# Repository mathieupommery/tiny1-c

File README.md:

Breakout board for the tiny1-c thermal sensor in order to get acces to Vospi pins.

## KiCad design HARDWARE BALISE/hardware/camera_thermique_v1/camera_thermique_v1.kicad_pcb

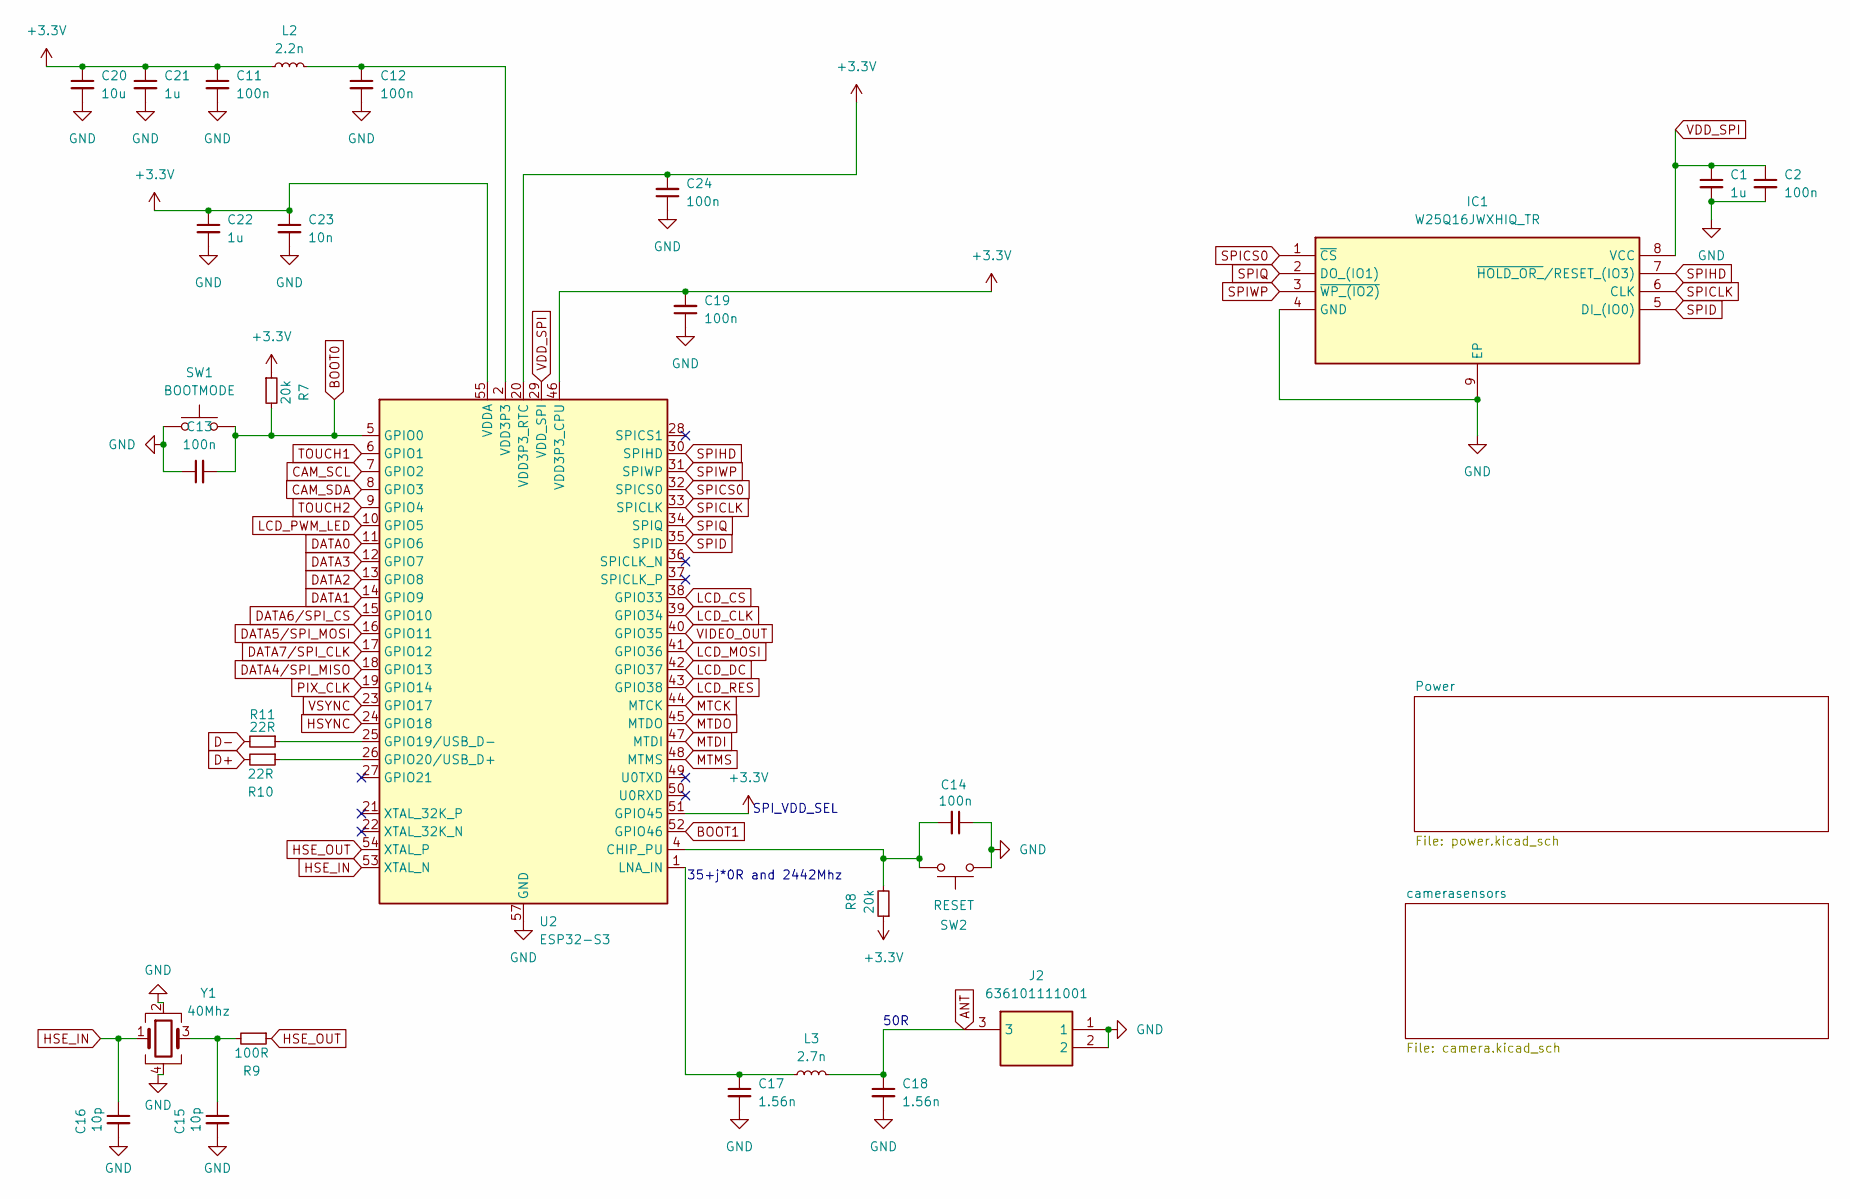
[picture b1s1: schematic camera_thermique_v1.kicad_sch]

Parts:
C1, C21, C22: 1u; C_0402_1005Metric_Pad0.74x0.62mm_HandSolder
C2, C11, C12, C13, C14, C19, C24: 100n; C_0201_0603Metric_Pad0.64x0.40mm_HandSolder
C15, C16: 10p; C_0201_0603Metric_Pad0.64x0.40mm_HandSolder
C17, C18: 1.56n; C_0402_1005Metric_Pad0.74x0.62mm_HandSolder
C20: 10u; C_0402_1005Metric_Pad0.74x0.62mm_HandSolder
C23: 10n; C_0201_0603Metric_Pad0.64x0.40mm_HandSolder
IC1: W25Q16JWXHIQ_TR; SON50P300X200X40-9N; Mouser Part Number 454-W25Q16JWXHIQTR
J2: 636101111001; Mouser Part Number 710-636101111001
L2: 2.2n; L_0603_1608Metric
L3: 2.7n; L_0603_1608Metric
R7, R8: 20k; R_0201_0603Metric_Pad0.64x0.40mm_HandSolder
R9: 100R; R_0201_0603Metric_Pad0.64x0.40mm_HandSolder
R10, R11: 22R; R_0201_0603Metric_Pad0.64x0.40mm_HandSolder
SW1: BOOTMODE; SW_KXT3
SW2: RESET; SW_KXT3
U2: ESP32-S3; QFN-56-1EP_7x7mm_P0.4mm_EP4x4mm
Y1: 40Mhz; LFXTAL069527REEL

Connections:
+3.3V: C11.1, C19.2, C20.1, C21.1, C22.1, C23.1, C24.2, L2.1, R7.1, R8.1, U2.20 (VDD3P3_RTC), U2.46 (VDD3P3_CPU), U2.51 (GPIO45), U2.55 (VDDA), U2.56 (VDDA); also elsewhere on the board
ANT: C18.1, J2.3, L3.2
BOOT0: C13.2, R7.2, SW1.2, U2.5 (GPIO0)
BOOT1: U2.52 (GPIO46)
CAM_SCL: U2.7 (GPIO2); also elsewhere on the board
CAM_SDA: U2.8 (GPIO3); also elsewhere on the board
D+: R10.2; also elsewhere on the board
D-: R11.2; also elsewhere on the board
DATA0: U2.11 (GPIO6); also elsewhere on the board
DATA1: U2.14 (GPIO9); also elsewhere on the board
DATA2: U2.13 (GPIO8); also elsewhere on the board
DATA3: U2.12 (GPIO7); also elsewhere on the board
DATA4/SPI_MISO: U2.18 (GPIO13); also elsewhere on the board
DATA5/SPI_MOSI: U2.16 (GPIO11); also elsewhere on the board
DATA6/SPI_CS: U2.15 (GPIO10); also elsewhere on the board
DATA7/SPI_CLK: U2.17 (GPIO12); also elsewhere on the board
GND: C1.2, C2.2, C11.2, C12.2, C13.1, C14.1, C15.2, C16.2, C17.2, C18.2, C19.1, C20.2, C21.2, C22.2, C23.2, C24.1, IC1.4 (GND), IC1.9 (EP), J2.1, J2.2, SW1.1, SW2.1, U2.57 (GND), Y1.2, Y1.4; also elsewhere on the board
HSE_IN: C16.1, U2.53 (XTAL_N), Y1.1
HSE_OUT: R9.1, U2.54 (XTAL_P)
HSYNC: U2.24 (GPIO18); also elsewhere on the board
LCD_CLK: U2.39 (GPIO34); also elsewhere on the board
LCD_CS: U2.38 (GPIO33); also elsewhere on the board
LCD_DC: U2.42 (GPIO37); also elsewhere on the board
LCD_MOSI: U2.41 (GPIO36); also elsewhere on the board
LCD_PWM_LED: U2.10 (GPIO5); also elsewhere on the board
LCD_RES: U2.43 (GPIO38); also elsewhere on the board
MTCK: U2.44 (MTCK)
MTDI: U2.47 (MTDI)
MTDO: U2.45 (MTDO)
MTMS: U2.48 (MTMS)
unnamed: C12.1, L2.2, U2.2 (VDD3P3), U2.3 (VDD3P3)
unnamed: C15.1, R9.2, Y1.3
unnamed: C14.2, R8.2, SW2.2, U2.4 (CHIP_PU)
unnamed: R11.1, U2.25 (GPIO19/USB_D-)
unnamed: R10.1, U2.26 (GPIO20/USB_D+)
unnamed: C17.1, L3.1, U2.1 (LNA_IN)
PIX_CLK: U2.19 (GPIO14); also elsewhere on the board
SPICLK: IC1.6 (CLK), U2.33 (SPICLK)
SPICS0: IC1.1 (~CS), U2.32 (SPICS0)
SPID: IC1.5 (DI_(IO0)), U2.35 (SPID)
SPIHD: IC1.7 (~HOLD_OR_/RESET_(IO3)), U2.30 (SPIHD)
SPIQ: IC1.2 (DO_(IO1)), U2.34 (SPIQ)
SPIWP: IC1.3 (~WP_(IO2)), U2.31 (SPIWP)
TOUCH1: U2.6 (GPIO1)
TOUCH2: U2.9 (GPIO4)
VDD_SPI: C1.1, C2.1, IC1.8 (VCC), U2.29 (VDD_SPI)
VIDEO_OUT: U2.40 (GPIO35)
VSYNC: U2.23 (GPIO17); also elsewhere on the board

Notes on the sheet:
35+j*0R and 2442Mhz
SPI_VDD_SEL
50R

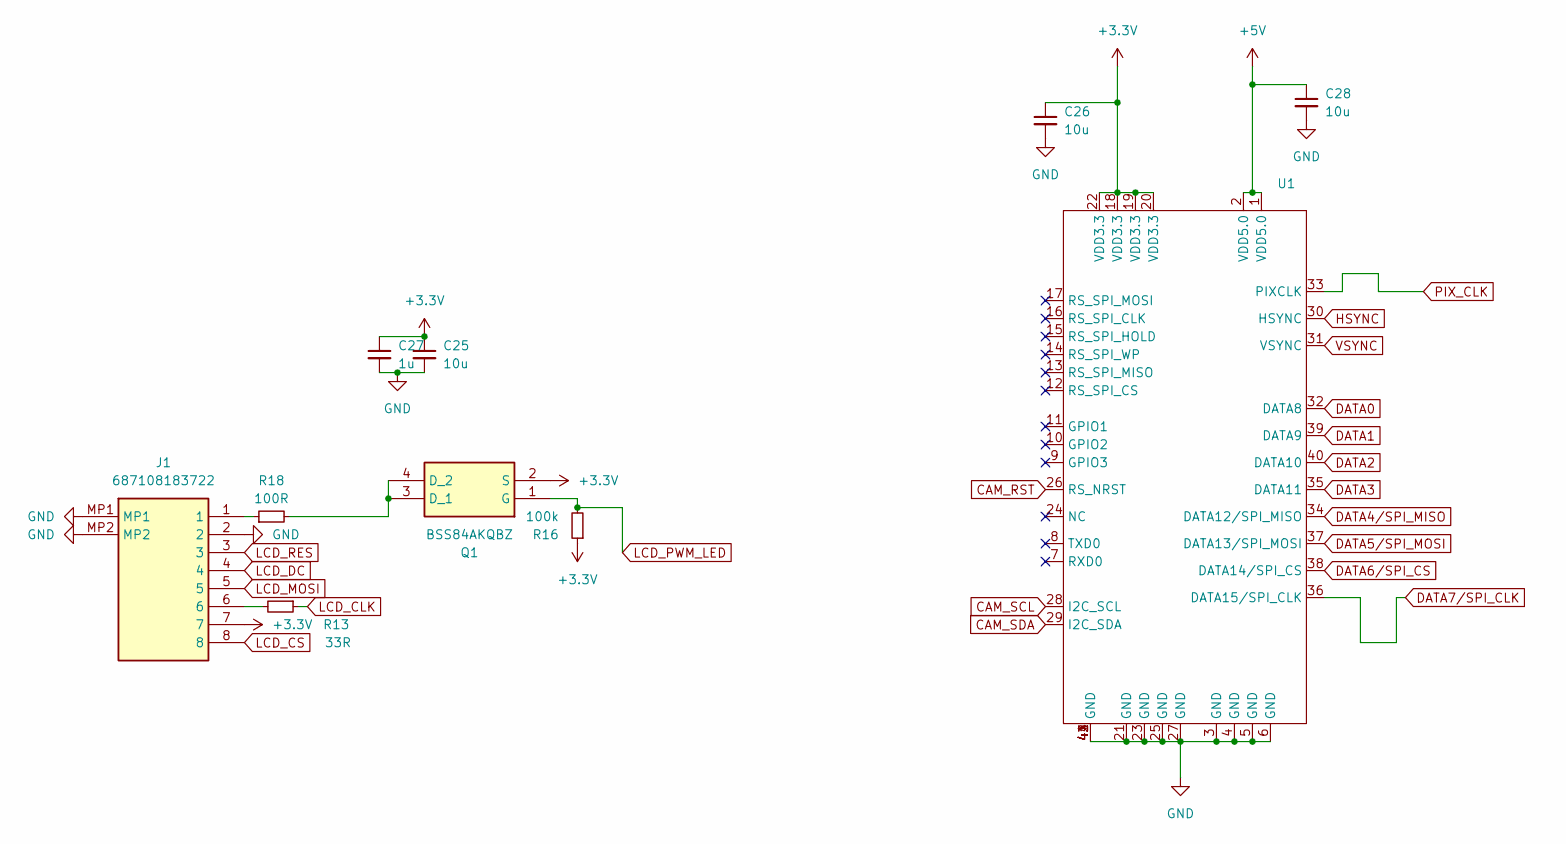
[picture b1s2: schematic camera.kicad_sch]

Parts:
C25, C26, C28: 10u; C_0402_1005Metric_Pad0.74x0.62mm_HandSolder
C27: 1u; C_0402_1005Metric_Pad0.74x0.62mm_HandSolder
J1: 687108183722; Mouser Part Number 710-687108183722
Q1: BSS84AKQBZ; 2N7002KQBZ; Mouser Part Number 771-2N7002KQBZ
R13: 33R; R_0201_0603Metric_Pad0.64x0.40mm_HandSolder
R16: 100k; R_0201_0603Metric_Pad0.64x0.40mm_HandSolder
R18: 100R; R_0201_0603Metric_Pad0.64x0.40mm_HandSolder
U1: tiny1c

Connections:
+3.3V: C25.1, C26.1, C27.1, J1.7, Q1.2 (S), R16.1, U1.18 (VDD3.3), U1.19 (VDD3.3), U1.20 (VDD3.3), U1.22 (VDD3.3); also elsewhere on the board
+5V: C28.1, U1.1 (VDD5.0), U1.2 (VDD5.0); also elsewhere on the board
CAM_RST: U1.26 (RS_NRST)
CAM_SCL: U1.28 (I2C_SCL); also elsewhere on the board
CAM_SDA: U1.29 (I2C_SDA); also elsewhere on the board
DATA0: U1.32 (DATA8); also elsewhere on the board
DATA1: U1.39 (DATA9); also elsewhere on the board
DATA2: U1.40 (DATA10); also elsewhere on the board
DATA3: U1.35 (DATA11); also elsewhere on the board
DATA4/SPI_MISO: U1.34 (DATA12/SPI_MISO); also elsewhere on the board
DATA5/SPI_MOSI: U1.37 (DATA13/SPI_MOSI); also elsewhere on the board
DATA6/SPI_CS: U1.38 (DATA14/SPI_CS); also elsewhere on the board
DATA7/SPI_CLK: U1.36 (DATA15/SPI_CLK); also elsewhere on the board
GND: C25.2, C26.2, C27.2, C28.2, J1.2, J1.MP1, J1.MP2, U1.3 (GND), U1.4 (GND), U1.5 (GND), U1.6 (GND), U1.21 (GND), U1.23 (GND), U1.25 (GND), U1.27 (GND), U1.41 (GND), U1.42 (GND), U1.43 (GND), U1.44 (GND); also elsewhere on the board
HSYNC: U1.30 (HSYNC); also elsewhere on the board
LCD_CLK: R13.1; also elsewhere on the board
LCD_CS: J1.8; also elsewhere on the board
LCD_DC: J1.4; also elsewhere on the board
LCD_MOSI: J1.5; also elsewhere on the board
LCD_PWM_LED: Q1.1 (G), R16.2; also elsewhere on the board
LCD_RES: J1.3; also elsewhere on the board
unnamed: J1.1, R18.1
unnamed: J1.6, R13.2
unnamed: Q1.3 (D_1), Q1.4 (D_2), R18.2
PIX_CLK: U1.33 (PIXCLK); also elsewhere on the board
VSYNC: U1.31 (VSYNC); also elsewhere on the board

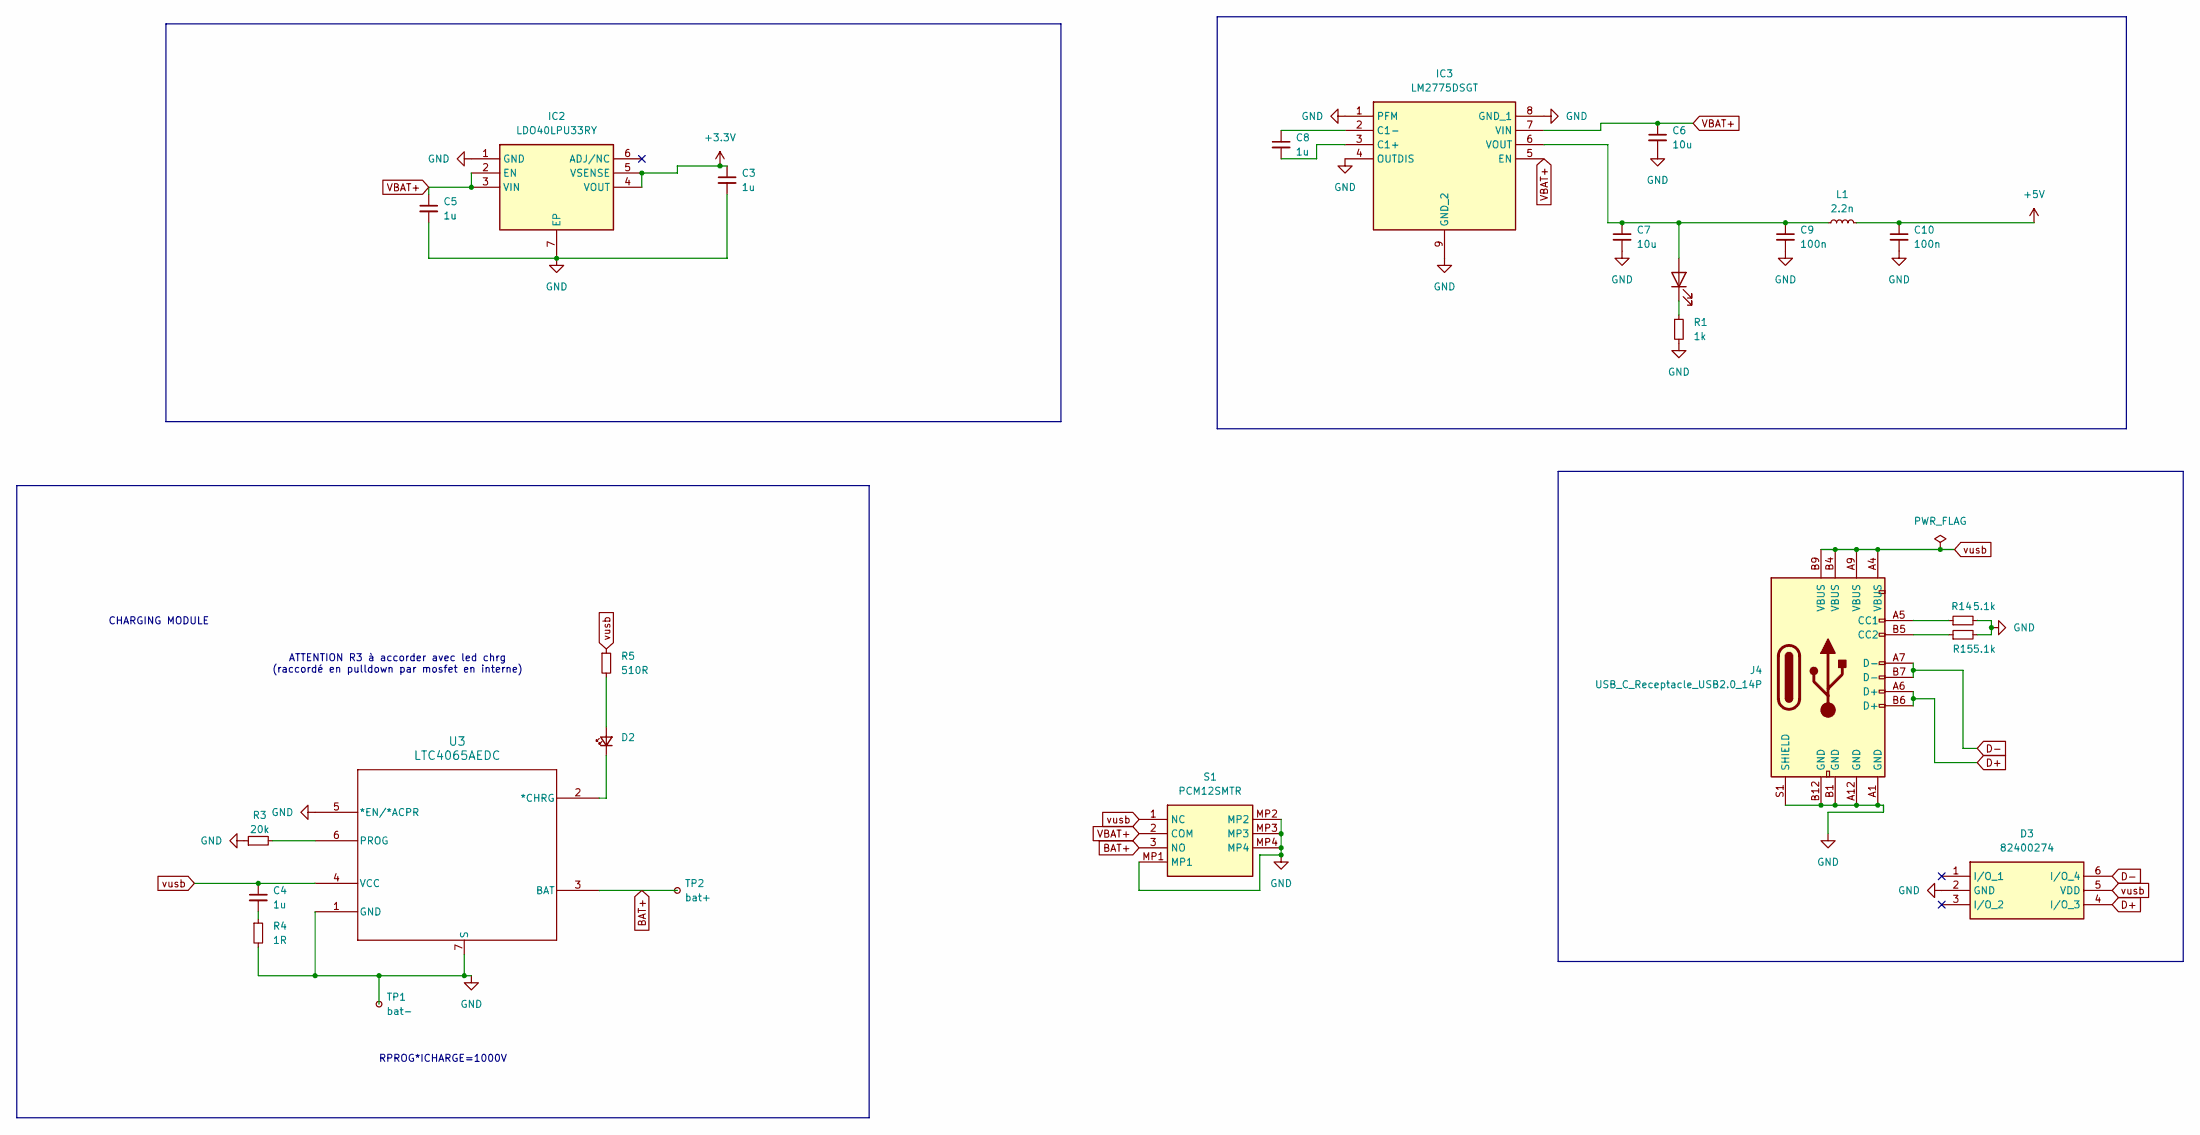
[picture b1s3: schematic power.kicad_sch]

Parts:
C3, C4, C5, C8: 1u; C_0402_1005Metric_Pad0.74x0.62mm_HandSolder
C6, C7: 10u; C_0402_1005Metric_Pad0.74x0.62mm_HandSolder
C9, C10: 100n; C_0402_1005Metric_Pad0.74x0.62mm_HandSolder
D1: LED; LED_0603_1608Metric
D2: LED_0603_1608Metric
D3: 82400274; SOT65P210X110-6N; Mouser Part Number 710-82400274
IC2: LDO40LPU33RY; SON95P300X300X90-7N-D; Mouser Part Number 511-LDO40LPU33RY
IC3: LM2775DSGT; SON50P200X200X80-9N; Mouser Part Number 595-LM2775DSGT
J4: USB_C_Receptacle_USB2.0_14P; WURTH_629722000214
L1: 2.2n; L_0603_1608Metric
R1: 1k; R_0201_0603Metric_Pad0.64x0.40mm_HandSolder
R3: 20k; R_0201_0603Metric_Pad0.64x0.40mm_HandSolder
R4: 1R; R_0201_0603Metric_Pad0.64x0.40mm_HandSolder
R5: 510R; R_0201_0603Metric_Pad0.64x0.40mm_HandSolder
R14, R15: 5.1k; R_0201_0603Metric_Pad0.64x0.40mm_HandSolder
S1: PCM12SMTR; Mouser Part Number 611-PCM12SMTR
TP1: bat-; TestPoint_THTPad_D1.0mm_Drill0.5mm
TP2: bat+; TestPoint_THTPad_D1.0mm_Drill0.5mm
U3: LTC4065AEDC; SON50P200X200X80-7N-D

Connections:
+3.3V: C3.1, IC2.4 (VOUT), IC2.5 (VSENSE); also elsewhere on the board
+5V: C10.1, L1.2; also elsewhere on the board
BAT+: S1.3 (NO), TP2.1, U3.3 (BAT)
D+: D3.4 (I/O_3), J4.A6 (D+), J4.B6 (D+); also elsewhere on the board
D-: D3.6 (I/O_4), J4.A7 (D-), J4.B7 (D-); also elsewhere on the board
GND: C3.2, C5.2, C6.2, C7.2, C9.2, C10.2, D3.2 (GND), IC2.1 (GND), IC2.7 (EP), IC3.1 (PFM), IC3.4 (OUTDIS), IC3.8 (GND_1), IC3.9 (GND_2), J4.A1 (GND), J4.A12 (GND), J4.B1 (GND), J4.B12 (GND), J4.S1 (SHIELD), R1.2, R3.1, R4.2, R14.2, R15.2, S1.MP1, S1.MP2, S1.MP3, S1.MP4, TP1.1, U3.1 (GND), U3.5 (*EN/*ACPR), U3.7 (S); also elsewhere on the board
unnamed: C4.2, R4.1
unnamed: C7.1, C9.1, D1.2 (A), IC3.6 (VOUT), L1.1
unnamed: D1.1 (K), R1.1
unnamed: D2.2 (A), R5.2
unnamed: D2.1 (K), U3.2 (*CHRG)
unnamed: C8.2, IC3.3 (C1+)
unnamed: C8.1, IC3.2 (C1-)
unnamed: J4.A5 (CC1), R14.1
unnamed: J4.B5 (CC2), R15.1
unnamed: R3.2, U3.6 (PROG)
VBAT+: C5.1, C6.1, IC2.2 (EN), IC2.3 (VIN), IC3.5 (EN), IC3.7 (VIN), S1.2 (COM)
vusb: C4.1, D3.5 (VDD), J4.A4 (VBUS), J4.A9 (VBUS), J4.B4 (VBUS), J4.B9 (VBUS), R5.1, S1.1 (NC), U3.4 (VCC)

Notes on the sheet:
CHARGING MODULE
RPROG*ICHARGE=1000V
ATTENTION R3 à accorder avec led chrg (raccordé en pulldown par mosfet en interne)

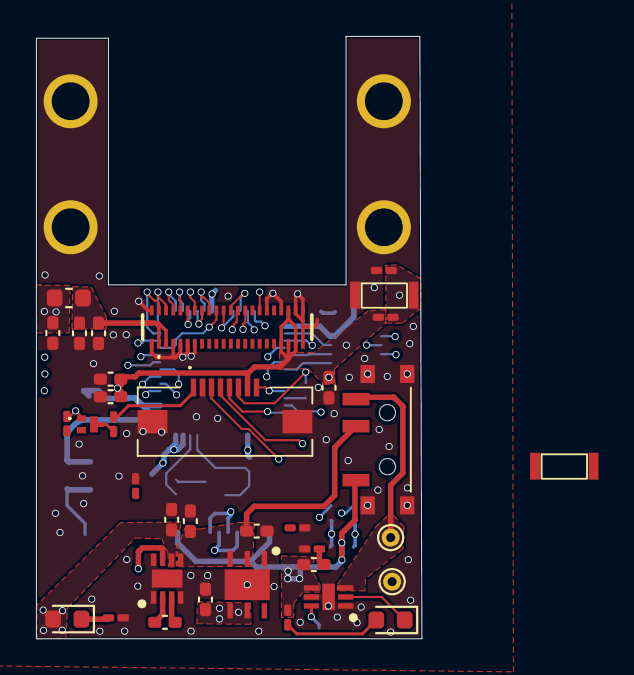
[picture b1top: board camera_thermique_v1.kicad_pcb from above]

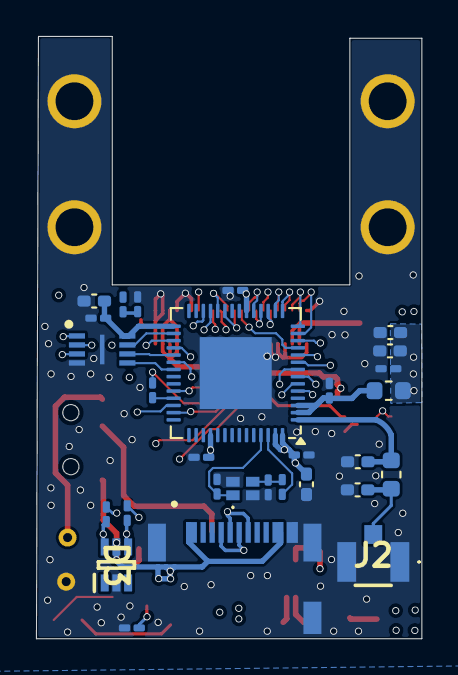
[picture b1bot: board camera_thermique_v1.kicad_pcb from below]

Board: 6 copper layers, 21.4 x 33.5 mm, 64 parts (29 on the bottom side), 57 nets.

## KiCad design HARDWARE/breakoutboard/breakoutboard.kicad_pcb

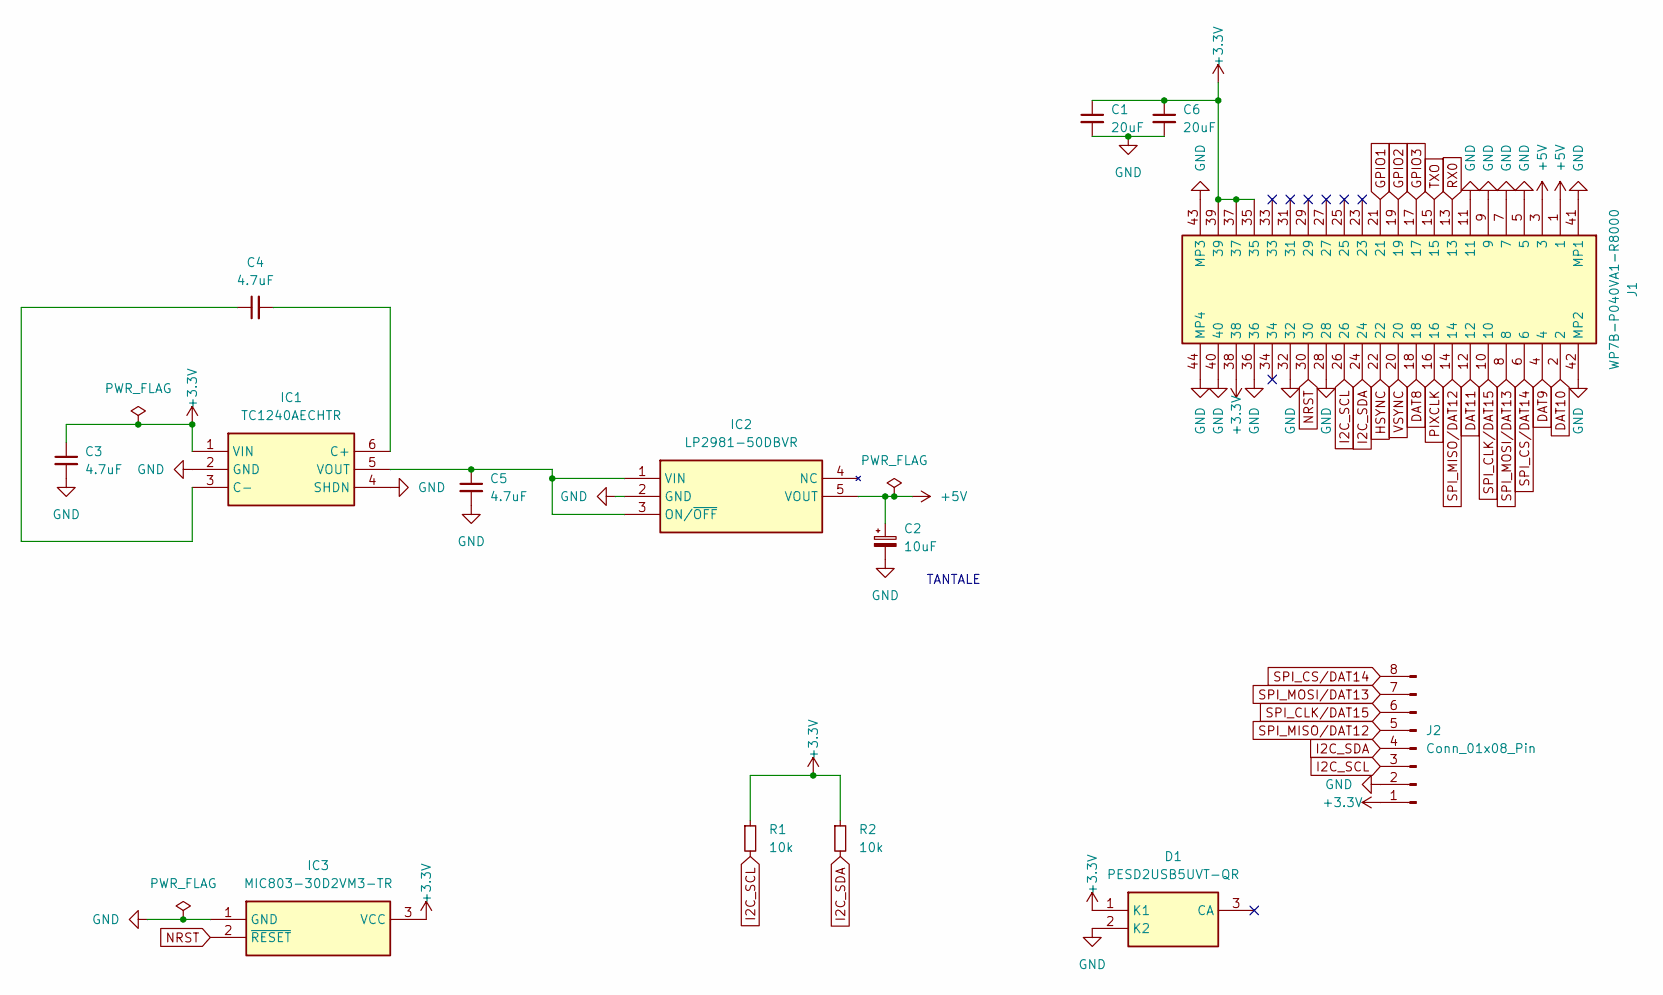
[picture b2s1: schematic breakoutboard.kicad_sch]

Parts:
C1, C6: 20uF; C_0603_1608Metric
C2: 10uF; CP_EIA-3216-18_Kemet-A
C3, C4: 4.7uF; C_0402_1005Metric
C5: 4.7uF; C_0603_1608Metric
D1: PESD2USB5UVT-QR; SOT95P230X110-3N; Mouser Part Number 771-PESD2USB5UVT-QR
IC1: TC1240AECHTR; SOT95P280X145-6N; Mouser Part Number 579-TC1240AECHTR
IC2: LP2981-50DBVR; SOT95P280X145-5N; Mouser Part Number 595-LP2981-50DBVR
IC3: MIC803-30D2VM3-TR; SOT95P237X111-3N; Mouser Part Number 998-MIC803-30D2VM3TR
J1: WP7B-P040VA1-R8000; WP7BP040VA1R8000; Mouser Part Number 656-WP7B-P040VA1-R8K
J2: Conn_01x08_Pin; JST_SH_SM08B-SRSS-TB_1x08-1MP_P1.00mm_Horizontal
R1, R2: 10k; R_0402_1005Metric_Pad0.72x0.64mm_HandSolder

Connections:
+3.3V: C1.1, C3.1, C6.1, D1.1 (K1), IC1.1 (VIN), IC3.3 (VCC), J1.35, J1.37, J1.38, J1.39, J2.1, R1.1, R2.1
+5V: C2.1, IC2.5 (VOUT), J1.1, J1.3
DAT8: J1.18
DAT9: J1.4
DAT10: J1.2
DAT11: J1.12
GND: C1.2, C2.2, C3.2, C5.2, C6.2, D1.2 (K2), IC1.2 (GND), IC1.4 (SHDN), IC2.2 (GND), IC3.1 (GND), J1.5, J1.7, J1.9, J1.11, J1.28, J1.32, J1.36, J1.40, J1.41 (MP1), J1.42 (MP2), J1.43 (MP3), J1.44 (MP4), J2.2, J2.MP
GPIO1: J1.21
GPIO2: J1.19
GPIO3: J1.17
HSYNC: J1.22
I2C_SCL: J1.26, J2.3, R1.2
I2C_SDA: J1.24, J2.4, R2.2
NRST: IC3.2 (~RESET), J1.30
unnamed: C4.2, IC1.6 (C+)
unnamed: C4.1, IC1.3 (C-)
unnamed: C5.1, IC1.5 (VOUT), IC2.1 (VIN), IC2.3 (ON/~OFF)
PIXCLK: J1.16
RX0: J1.13
SPI_CLK/DAT15: J1.10, J2.6
SPI_CS/DAT14: J1.6, J2.8
SPI_MISO/DAT12: J1.14, J2.5
SPI_MOSI/DAT13: J1.8, J2.7
TXO: J1.15
VSYNC: J1.20

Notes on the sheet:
TANTALE

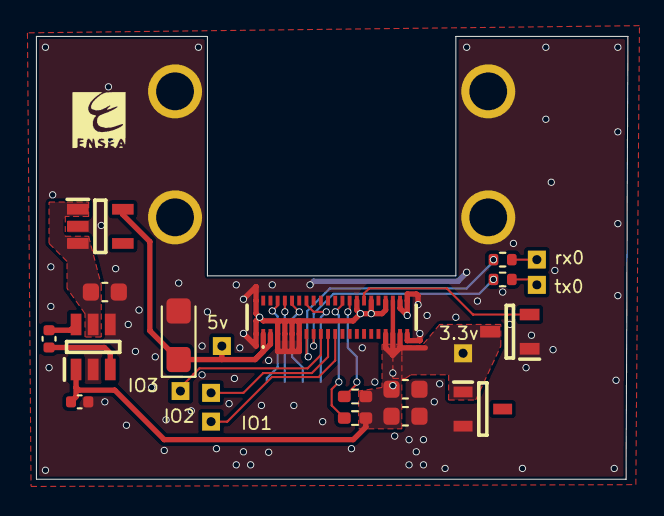
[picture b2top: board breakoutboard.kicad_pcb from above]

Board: 2 copper layers, 32.9 x 24.6 mm, 14 parts (1 on the bottom side), 13 nets.
